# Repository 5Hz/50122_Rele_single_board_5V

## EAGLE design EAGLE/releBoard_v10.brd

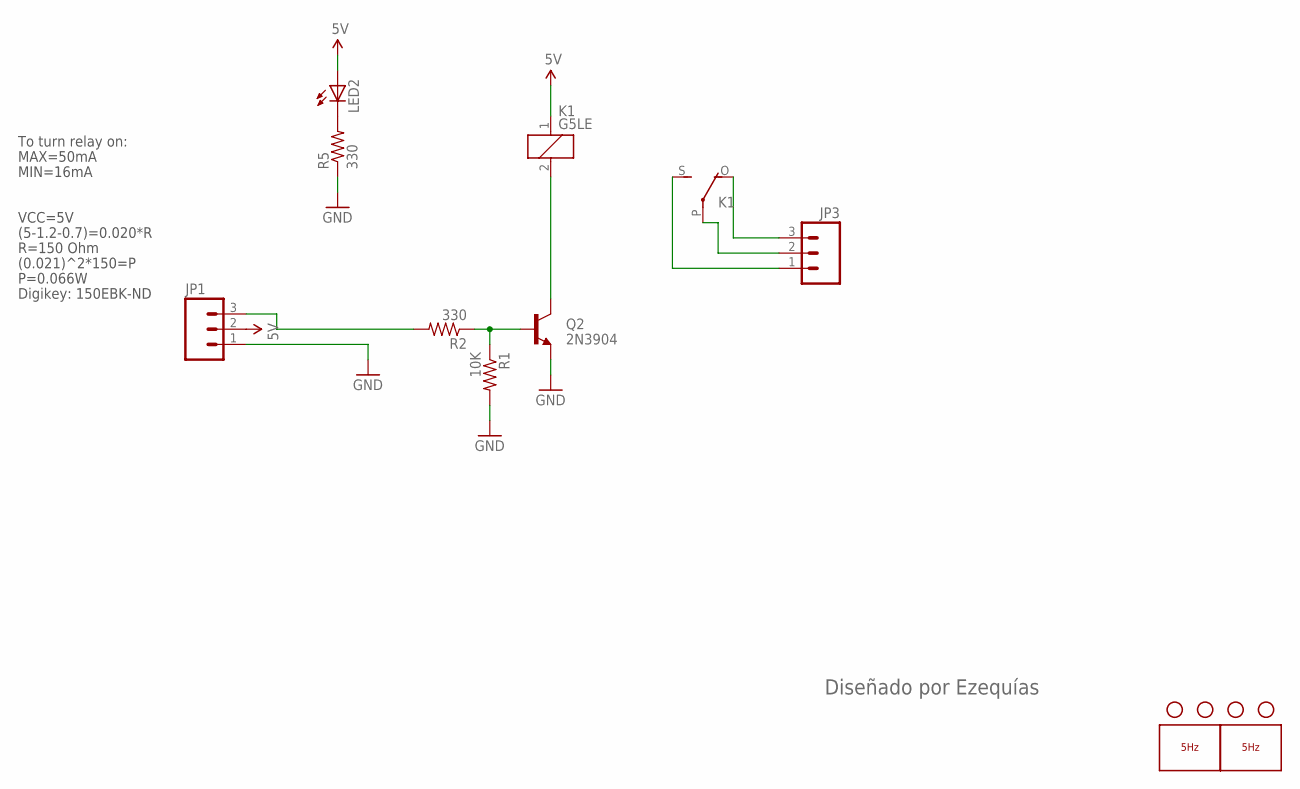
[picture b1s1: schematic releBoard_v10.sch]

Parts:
JP1: M03POLAR; MOLEX-1X3
JP3: M03-SCREW-5MM; SCREWTERMINAL-5MM-3
K1: G5LE
LED2: LED0603; LED-0603
LOGO1: LOGO_5HZ_H_15MM; 5HZ_LOGO_H_15MM
LOGO2: LOGO_5HZ_WEB_COOPER_10MM; 5HZ_WEB_COOPER_10MM
Q2: 2N3904; SOT23
R1: 10K; 0603-RES
R2, R5: 330; 0603-RES
U$3, U$4, U$5, U$7: STAND-OFF

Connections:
5V: JP1.2, K1.1, LED2.A
COIL: K1.2, Q2.3 (C)
GND: JP1.1, Q2.2 (E), R1.2, R5.1
LINE: JP3.2, K1.P
unnamed: JP1.3, R2.2
unnamed: LED2.C, R5.2
unnamed: Q2.1 (B), R1.1, R2.1
NC: JP3.3, K1.O
NO: JP3.1, K1.S

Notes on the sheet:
To turn relay on:
(5-1.2-0.7)=0.020*R
R=150 Ohm
VCC=5V
MAX=50mA
MIN=16mA
(0.021)^2*150=P
P=0.066W
Digikey: 150EBK-ND
Diseñado por Ezequías

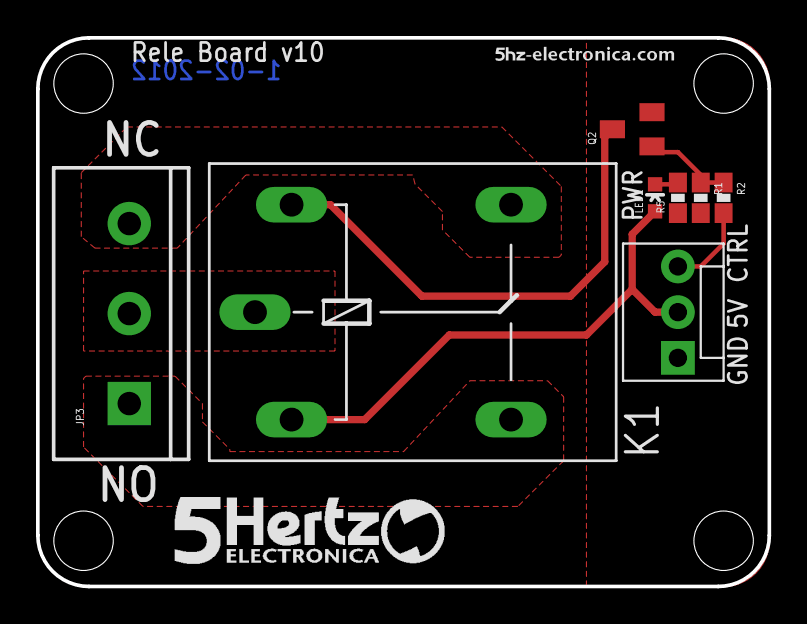
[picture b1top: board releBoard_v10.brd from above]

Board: 2 copper layers, 40.6 x 30.5 mm, 14 parts (0 on the bottom side), 9 nets.

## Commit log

2014-01-14 creación
